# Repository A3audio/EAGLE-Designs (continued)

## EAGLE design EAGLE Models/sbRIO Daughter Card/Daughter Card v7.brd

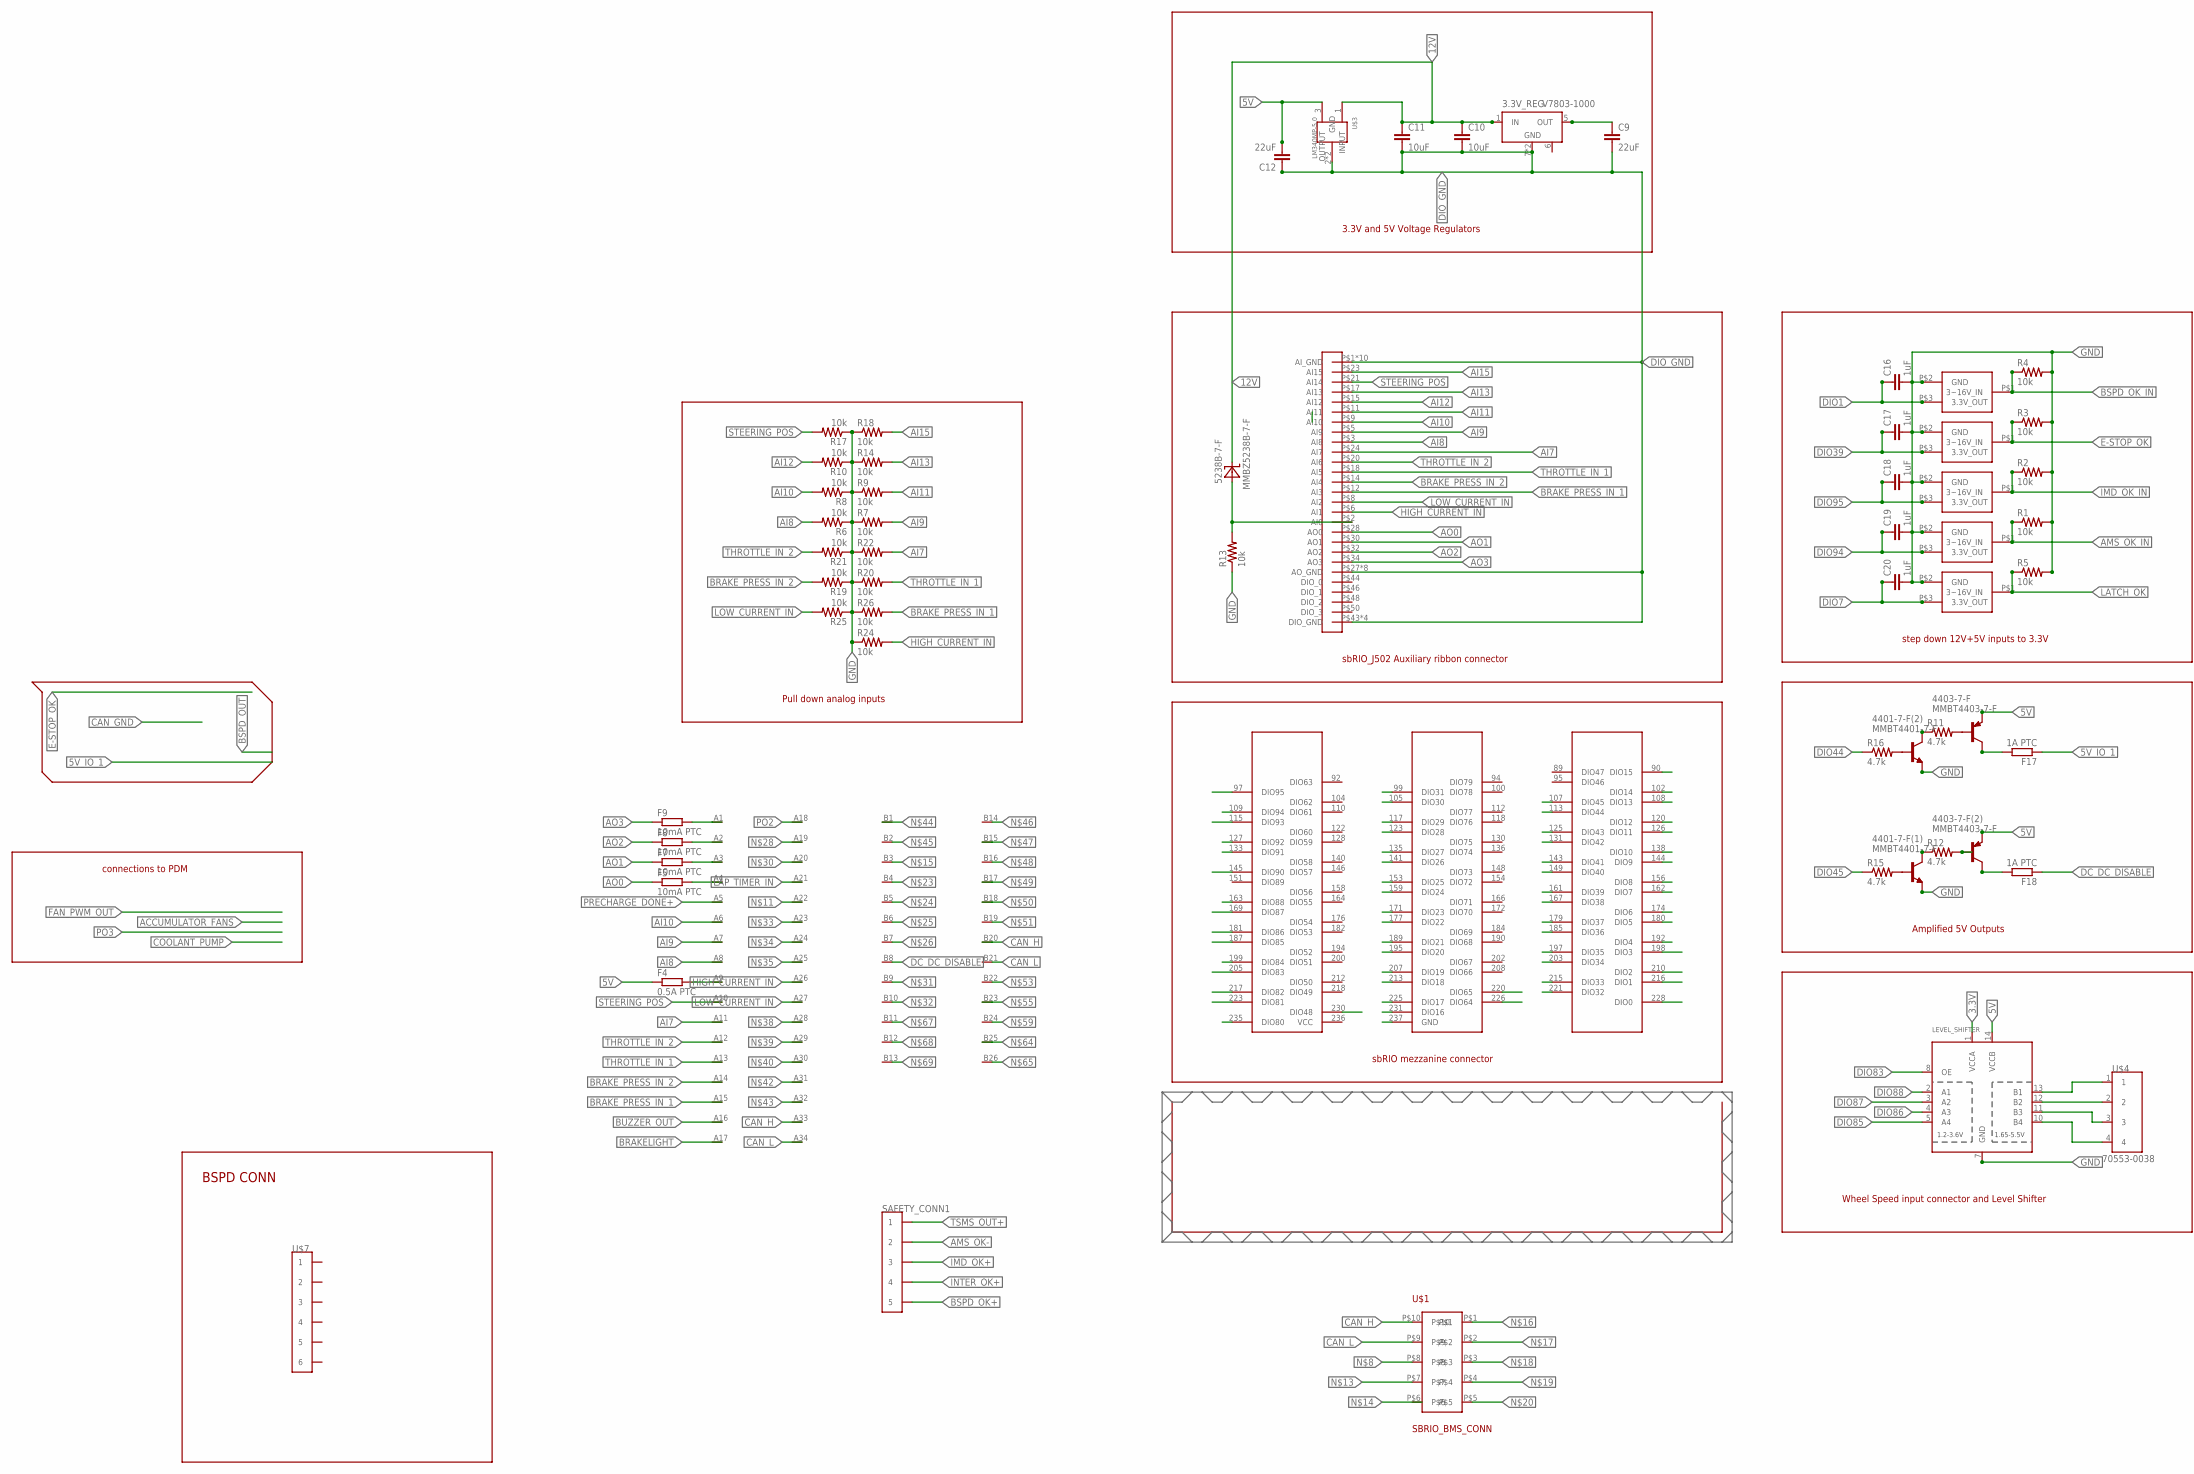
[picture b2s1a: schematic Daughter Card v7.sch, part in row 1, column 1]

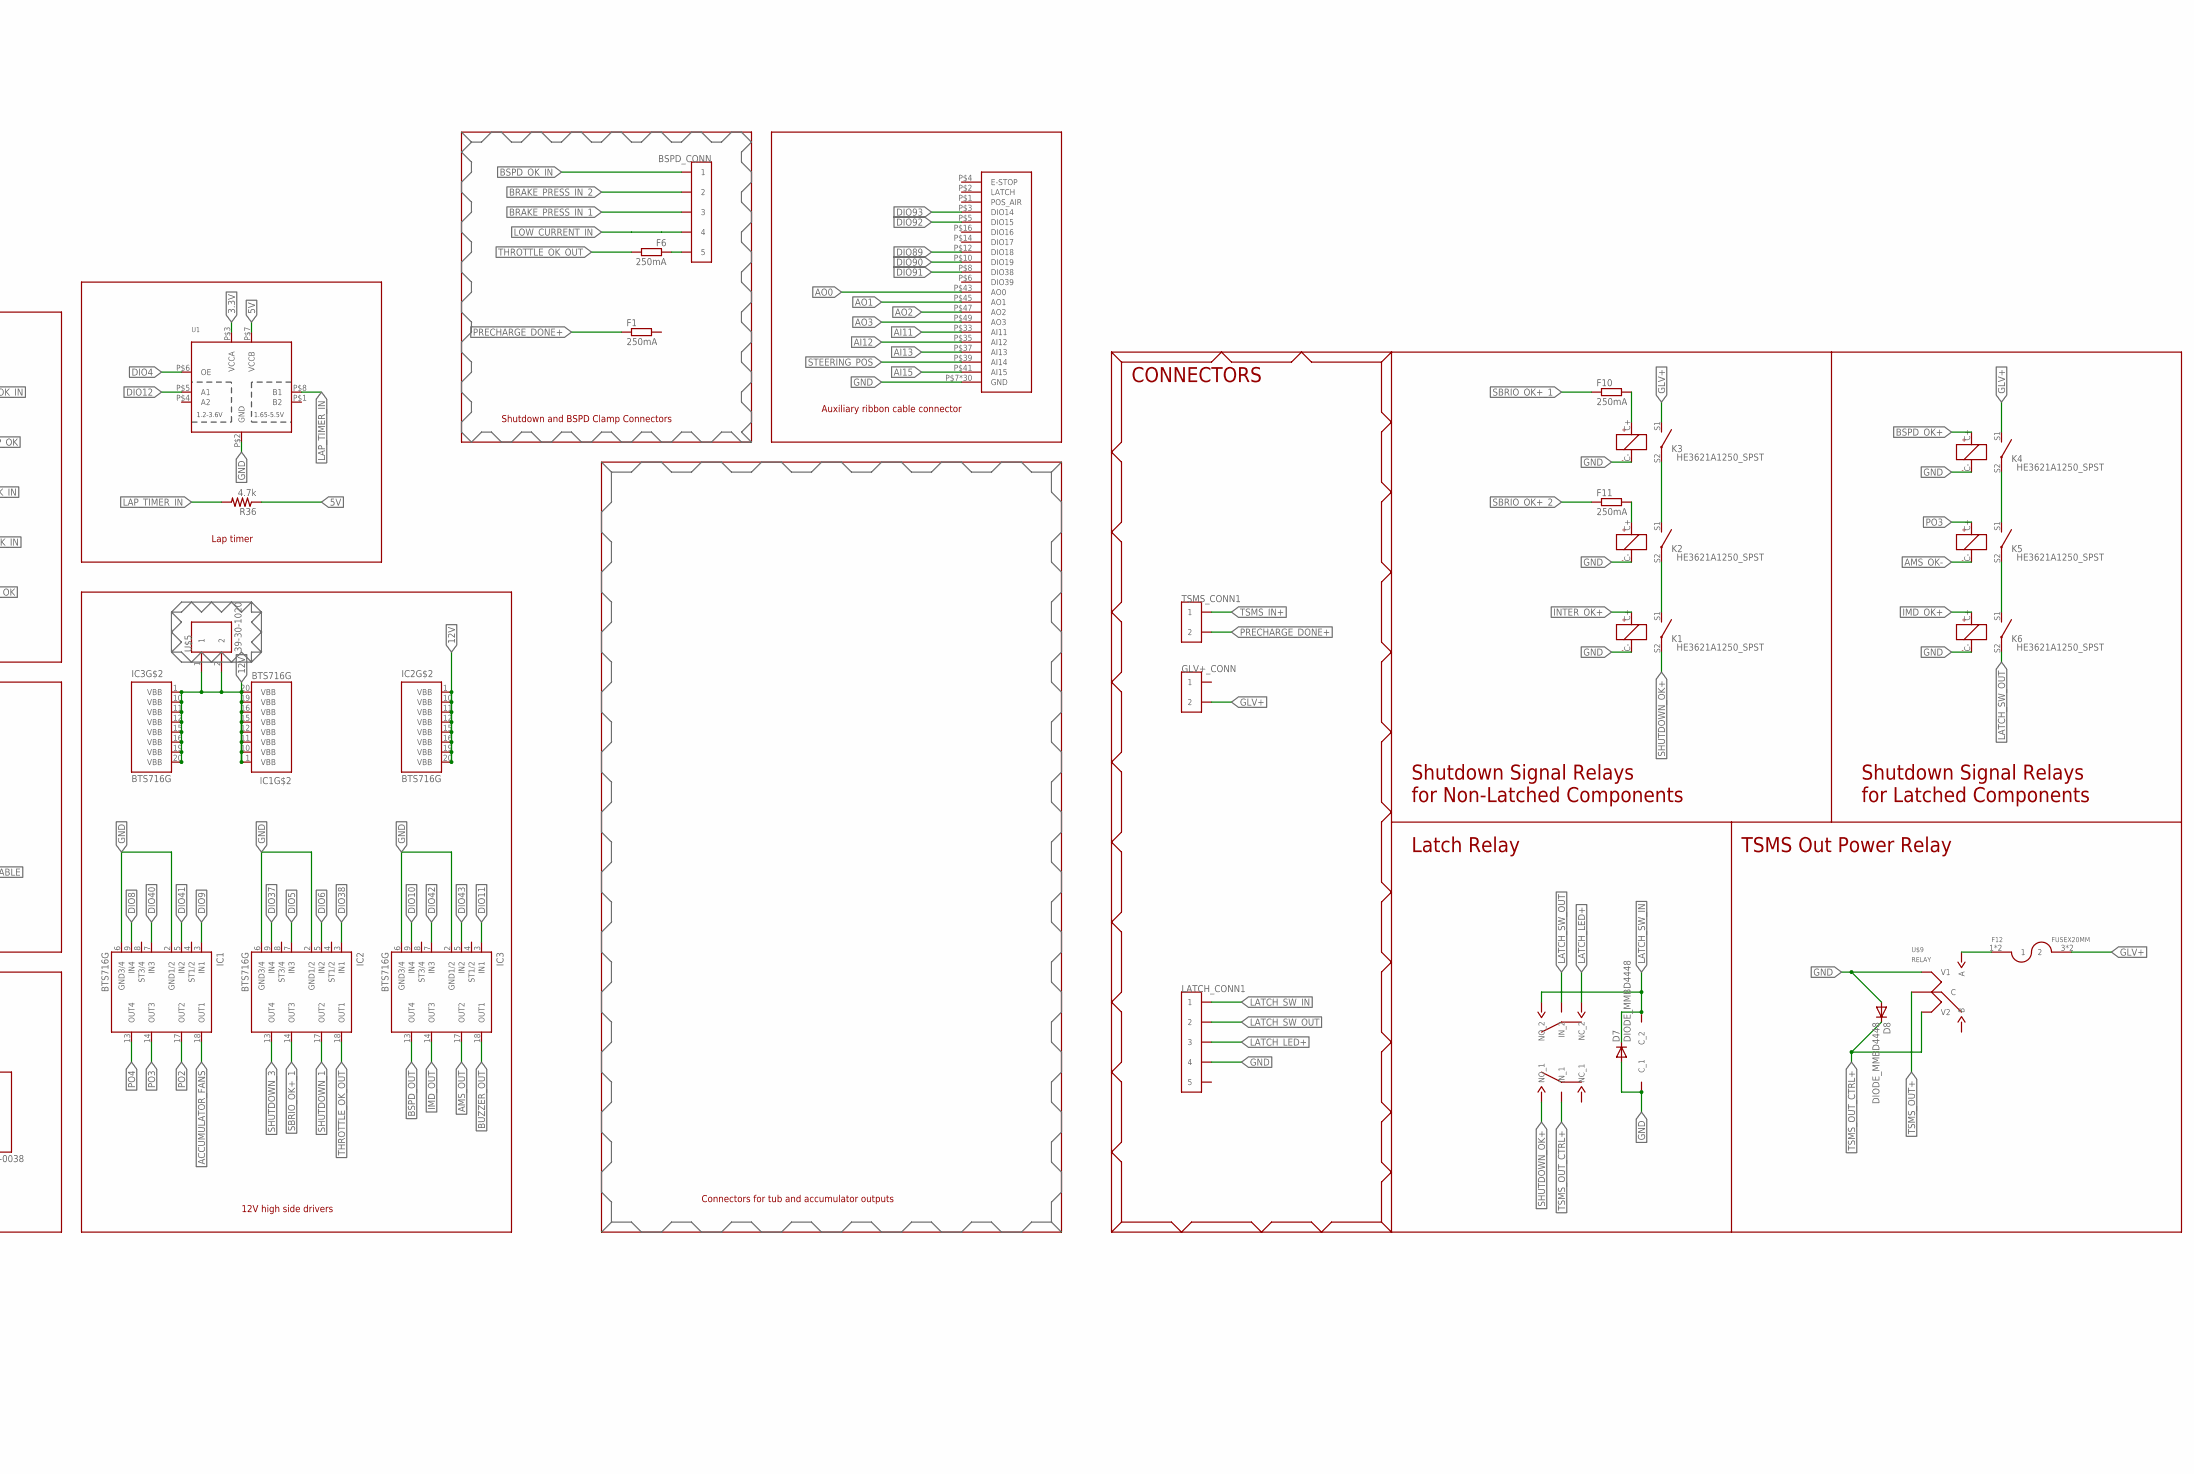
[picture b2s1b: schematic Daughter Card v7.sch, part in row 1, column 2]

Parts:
3.3V_REG: V7803-1000; V78XX-1000
4401-7-F(1), 4401-7-F(2): MMBT4401-7-F; SOT-23-3@1
4403-7-F, 4403-7-F(2): MMBT4403-7-F; SOT-23-3@1
5225-3.3M5-TR(5), 5525-3.3YM5-TR(1), 5525-3.3YM5-TR(2), 5525-3.3YM5-TR(3), 5525-3.3YM5-TR(4): MIC5225-3.3YM5-TR; SOT-23-3@1
5238B-7-F: MMBZ5238B-7-F; SOT-23-3@1
BSPD_CONN: CONN_5; CONNECTOR_5
C9, C12: 22uF; 0603-CAP
C10, C11: 10uF; 0603-CAP
C16, C17, C18, C19, C20: 1uF; 0603-CAP
D7, D8: DIODE_MMBD4448; SOT-23-3
F1, F6, F10, F11: 250mA; R0603
F4: 0.5A PTC; R0603
F5, F7, F8, F9: 10mA PTC; R0402
F12: FUSEX20MM; FUSE_5MM
F17, F18: 1A PTC; R0603
GLV+_CONN: CONN_2; CONNECTOR_2
IC1, IC2, IC3: BTS716G; PG-DSO-20
K1, K2, K3, K4, K5, K6: HE3621A1250_SPST
LATCH_CONN1: CONN_5; CONNECTOR_5
LATCH_U1: JW2SN-DC12V; DPDT_JW2_FORM_C
LEVEL_SHIFTER: TXB0104PWR; TSSOP14
R1, R2, R3, R4, R5, R6, R7, R8, R9, R10, R13, R14, R17, R18, R19, R20, R21, R22, R24, R25, R26: 10k; R0402
R11, R12, R15, R16, R36: 4.7k; R0402
SAFETY_CONN1: CONN_5; CONNECTOR_5
SBRIO_ANALOG: SBRIO_MIO; SBRIO_J502_J503
SBRIO_AUX: SBRIO_AUX; SBRIO_J502_J503
SBRIO_MEZZANINE: SBRIO_RMC; SEAM-40-XX.X-XX-06-X-A
TSMS_CONN1: CONN_2; CONNECTOR_2
U1: TXS0102; VFSOP-8
U$1: SBRIO_BMS_CONN; SBRIO_W
U$3: LM340MP-5.0; SOT223-4
U$4: 70553-0038; MOLEX_70553-0038
U$5: 39-30-1020; MOLEX_39-30-1020
U$6: SUPERSEAL1.0_60POS
U$7: SULLINS_1MM_6P_HEADER; SULLINS_1MM_HEADER
U$9: RELAY

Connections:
3.3V: LEVEL_SHIFTER.1 (VCCA), U1.P$3 (VCCA)
5V: 4403-7-F.P$3 (E), 4403-7-F(2).P$3 (E), C12.2, F4.1, LEVEL_SHIFTER.14 (VCCB), R36.1, U1.P$7 (VCCB), U$3.3 (OUTPUT)
5V_IO_1: F17.1
12V: 3.3V_REG.1 (IN), 5238B-7-F.P$1 (C), C10.1, C11.1, IC1.1 (VBB), IC1.10 (VBB), IC1.11 (VBB), IC1.12 (VBB), IC1.15 (VBB), IC1.16 (VBB), IC1.19 (VBB), IC1.20 (VBB), IC2.1 (VBB), IC2.10 (VBB), IC2.11 (VBB), IC2.12 (VBB), IC2.15 (VBB), IC2.16 (VBB), IC2.19 (VBB), IC2.20 (VBB), IC3.1 (VBB), IC3.10 (VBB), IC3.11 (VBB), IC3.12 (VBB), IC3.15 (VBB), IC3.16 (VBB), IC3.19 (VBB), IC3.20 (VBB), U$3.1 (INPUT), U$5.1, U$5.2
ACCUMULATOR_FANS: IC1.18 (OUT1)
AI7: R22.2, SBRIO_ANALOG.P$24 (AI7), U$6.A11
AI8: R6.2, SBRIO_ANALOG.P$3 (AI8), U$6.A8
AI9: R7.2, SBRIO_ANALOG.P$5 (AI9), U$6.A7
AI10: R8.2, SBRIO_ANALOG.P$9 (AI10), U$6.A6
AI11: R9.2, SBRIO_ANALOG.P$11 (AI11), SBRIO_AUX.P$33 (AI11)
AI12: R10.2, SBRIO_ANALOG.P$15 (AI12), SBRIO_AUX.P$35 (AI12)
AI13: R14.2, SBRIO_ANALOG.P$17 (AI13), SBRIO_AUX.P$37 (AI13)
AI15: R18.2, SBRIO_ANALOG.P$23 (AI15), SBRIO_AUX.P$41 (AI15)
AMS_OK-: K5.C-, SAFETY_CONN1.3 (2), SAFETY_CONN1.4 (2)
AMS_OK_IN: 5525-3.3YM5-TR(1).P$1 (3~16V_IN), R1.1
AMS_OUT: IC3.17 (OUT2)
AO0: F5.1, SBRIO_ANALOG.P$28 (AO0), SBRIO_AUX.P$43 (AO0)
AO1: F7.1, SBRIO_ANALOG.P$30 (AO1), SBRIO_AUX.P$45 (AO1)
AO2: F8.1, SBRIO_ANALOG.P$32 (AO2), SBRIO_AUX.P$47 (AO2)
AO3: F9.1, SBRIO_ANALOG.P$34 (AO3), SBRIO_AUX.P$49 (AO3)
BRAKELIGHT: U$6.A17
BRAKE_PRESS_IN_1: BSPD_CONN.5 (3), BSPD_CONN.6 (3), R26.2, SBRIO_ANALOG.P$12 (AI3), U$6.A15
BRAKE_PRESS_IN_2: BSPD_CONN.3 (2), BSPD_CONN.4 (2), R19.2, SBRIO_ANALOG.P$14 (AI4), U$6.A14
BSPD_OK+: K4.C+, SAFETY_CONN1.9 (5), SAFETY_CONN1.10 (5)
BSPD_OK_IN: 5525-3.3YM5-TR(3).P$1 (3~16V_IN), BSPD_CONN.1, BSPD_CONN.2 (1), R4.1
BSPD_OUT: IC3.13 (OUT4)
BUZZER_OUT: IC3.18 (OUT1), U$6.A16
CAN_H: U$1.P$10, U$6.A33, U$6.B20
CAN_L: U$1.P$9, U$6.A34, U$6.B21
DC_DC_DISABLE: F18.1, U$6.B8
DIO0: SBRIO_MEZZANINE.228 (DIO0)
DIO1: 5525-3.3YM5-TR(3).P$3 (3.3V_OUT), C16.1, SBRIO_MEZZANINE.216 (DIO1)
DIO2: SBRIO_MEZZANINE.210 (DIO2)
DIO3: SBRIO_MEZZANINE.198 (DIO3)
DIO4: SBRIO_MEZZANINE.192 (DIO4), U1.P$6 (OE)
DIO5: IC2.7 (IN3), SBRIO_MEZZANINE.180 (DIO5)
DIO6: IC2.5 (IN2), SBRIO_MEZZANINE.174 (DIO6)
DIO7: 5525-3.3YM5-TR(2).P$3 (3.3V_OUT), C20.1, SBRIO_MEZZANINE.162 (DIO7)
DIO8: IC1.9 (IN4), SBRIO_MEZZANINE.156 (DIO8)
DIO9: IC1.3 (IN1), SBRIO_MEZZANINE.144 (DIO9)
DIO10: IC3.9 (IN4), SBRIO_MEZZANINE.138 (DIO10)
DIO11: IC3.3 (IN1), SBRIO_MEZZANINE.126 (DIO11)
DIO12: SBRIO_MEZZANINE.120 (DIO12), U1.P$5 (A1)
DIO13: SBRIO_MEZZANINE.108 (DIO13)
DIO14: SBRIO_MEZZANINE.102 (DIO14)
DIO15: SBRIO_MEZZANINE.90 (DIO15)
DIO16: SBRIO_MEZZANINE.231 (DIO16)
DIO17: SBRIO_MEZZANINE.225 (DIO17)
DIO18: SBRIO_MEZZANINE.213 (DIO18)
DIO19: SBRIO_MEZZANINE.207 (DIO19)
DIO20: SBRIO_MEZZANINE.195 (DIO20)
DIO21: SBRIO_MEZZANINE.189 (DIO21)
DIO22: SBRIO_MEZZANINE.177 (DIO22)
DIO23: SBRIO_MEZZANINE.171 (DIO23)
DIO24: SBRIO_MEZZANINE.159 (DIO24)
DIO25: SBRIO_MEZZANINE.153 (DIO25)
DIO26: SBRIO_MEZZANINE.141 (DIO26)
DIO27: SBRIO_MEZZANINE.135 (DIO27)
DIO28: SBRIO_MEZZANINE.123 (DIO28)
DIO29: SBRIO_MEZZANINE.117 (DIO29)
DIO30: SBRIO_MEZZANINE.105 (DIO30)
DIO31: SBRIO_MEZZANINE.99 (DIO31)
DIO32: SBRIO_MEZZANINE.221 (DIO32)
DIO33: SBRIO_MEZZANINE.215 (DIO33)
DIO34: SBRIO_MEZZANINE.203 (DIO34)
DIO35: SBRIO_MEZZANINE.197 (DIO35)
DIO36: SBRIO_MEZZANINE.185 (DIO36)
DIO37: IC2.9 (IN4), SBRIO_MEZZANINE.179 (DIO37)
DIO38: IC2.3 (IN1), SBRIO_MEZZANINE.167 (DIO38)
DIO39: 5525-3.3YM5-TR(4).P$3 (3.3V_OUT), C17.1, SBRIO_MEZZANINE.161 (DIO39)
DIO40: IC1.7 (IN3), SBRIO_MEZZANINE.149 (DIO40)
DIO41: IC1.5 (IN2), SBRIO_MEZZANINE.143 (DIO41)
DIO42: IC3.7 (IN3), SBRIO_MEZZANINE.131 (DIO42)
DIO43: IC3.5 (IN2), SBRIO_MEZZANINE.125 (DIO43)
DIO44: R16.1, SBRIO_MEZZANINE.113 (DIO44)
DIO45: R15.1, SBRIO_MEZZANINE.107 (DIO45)
DIO48: SBRIO_MEZZANINE.230 (DIO48)
DIO64: SBRIO_MEZZANINE.226 (DIO64)
DIO65: SBRIO_MEZZANINE.220 (DIO65)
DIO80: SBRIO_MEZZANINE.235 (DIO80)
DIO81: SBRIO_MEZZANINE.223 (DIO81)
DIO82: SBRIO_MEZZANINE.217 (DIO82)
DIO83: LEVEL_SHIFTER.8 (OE), SBRIO_MEZZANINE.205 (DIO83)
DIO84: SBRIO_MEZZANINE.199 (DIO84)
DIO85: LEVEL_SHIFTER.5 (A4), SBRIO_MEZZANINE.187 (DIO85)
DIO86: LEVEL_SHIFTER.4 (A3), SBRIO_MEZZANINE.181 (DIO86)
DIO87: LEVEL_SHIFTER.3 (A2), SBRIO_MEZZANINE.169 (DIO87)
DIO88: LEVEL_SHIFTER.2 (A1), SBRIO_MEZZANINE.163 (DIO88)
DIO89: SBRIO_AUX.P$12 (DIO18)
DIO90: SBRIO_AUX.P$10 (DIO19), SBRIO_MEZZANINE.145 (DIO90)
DIO91: SBRIO_AUX.P$8 (DIO38), SBRIO_MEZZANINE.133 (DIO91)
DIO92: SBRIO_AUX.P$5 (DIO15), SBRIO_MEZZANINE.127 (DIO92)
DIO93: SBRIO_AUX.P$3 (DIO14), SBRIO_MEZZANINE.115 (DIO93)
DIO94: 5525-3.3YM5-TR(1).P$3 (3.3V_OUT), C19.1, SBRIO_MEZZANINE.109 (DIO94)
DIO95: 5225-3.3M5-TR(5).P$3 (3.3V_OUT), C18.1, SBRIO_MEZZANINE.97 (DIO95)
DIO_GND: 3.3V_REG.7 (GND), 3.3V_REG.9 (GND), C9.2, C10.2, C11.2, C12.1, SBRIO_ANALOG.P$1 (AI_GND), SBRIO_ANALOG.P$4 (AI_GND), SBRIO_ANALOG.P$7 (AI_GND), SBRIO_ANALOG.P$10 (AI_GND), SBRIO_ANALOG.P$13 (AI_GND), SBRIO_ANALOG.P$16 (AI_GND), SBRIO_ANALOG.P$19 (AI_GND), SBRIO_ANALOG.P$22 (AI_GND), SBRIO_ANALOG.P$25 (AI_GND), SBRIO_ANALOG.P$26 (AI_GND), SBRIO_ANALOG.P$27 (AO_GND), SBRIO_ANALOG.P$29 (AO_GND), SBRIO_ANALOG.P$31 (AO_GND), SBRIO_ANALOG.P$33 (AO_GND), SBRIO_ANALOG.P$35 (AO_GND), SBRIO_ANALOG.P$37 (AO_GND), SBRIO_ANALOG.P$39 (AO_GND), SBRIO_ANALOG.P$41 (AO_GND), SBRIO_ANALOG.P$43 (DIO_GND), SBRIO_ANALOG.P$45 (DIO_GND), SBRIO_ANALOG.P$47 (DIO_GND), SBRIO_ANALOG.P$49 (DIO_GND), U$3.2 (GND), U$3.4 (GND)
E-STOP_OK: 5525-3.3YM5-TR(4).P$1 (3~16V_IN), R3.1
GLV+: F12.3 (2), F12.4 (2), GLV+_CONN.3 (2), GLV+_CONN.4 (2), K3.S1 (SW_1), K4.S1 (SW_1)
GND: 4401-7-F(1).P$3 (E), 4401-7-F(2).P$3 (E), 5225-3.3M5-TR(5).P$2 (GND), 5525-3.3YM5-TR(1).P$2 (GND), 5525-3.3YM5-TR(2).P$2 (GND), 5525-3.3YM5-TR(3).P$2 (GND), 5525-3.3YM5-TR(4).P$2 (GND), C16.2, C17.2, C18.2, C19.2, C20.2, D7.P$2 (A), D8.P$2 (A), IC1.2 (GND1/2), IC1.6 (GND3/4), IC2.2 (GND1/2), IC2.6 (GND3/4), IC3.2 (GND1/2), IC3.6 (GND3/4), K1.C-, K2.C-, K3.C-, K4.C-, K6.C-, LATCH_CONN1.7 (4), LATCH_CONN1.8 (4), LATCH_U1.COIL_1 (C_1), LEVEL_SHIFTER.7 (GND), R1.2, R2.2, R3.2, R4.2, R5.2, R6.1, R7.1, R8.1, R9.1, R10.1, R13.1, R14.1, R17.1, R18.1, R19.1, R20.1, R21.1, R22.1, R24.1, R25.1, R26.1, SBRIO_AUX.P$7 (GND), SBRIO_AUX.P$9 (GND), SBRIO_AUX.P$11 (GND), SBRIO_AUX.P$13 (GND), SBRIO_AUX.P$15 (GND), SBRIO_AUX.P$17 (GND), SBRIO_AUX.P$18 (GND), SBRIO_AUX.P$19 (GND), SBRIO_AUX.P$20 (GND), SBRIO_AUX.P$21 (GND), SBRIO_AUX.P$22 (GND), SBRIO_AUX.P$23 (GND), SBRIO_AUX.P$24 (GND), SBRIO_AUX.P$25 (GND), SBRIO_AUX.P$26 (GND), SBRIO_AUX.P$27 (GND), SBRIO_AUX.P$28 (GND), SBRIO_AUX.P$29 (GND), SBRIO_AUX.P$30 (GND), SBRIO_AUX.P$31 (GND), SBRIO_AUX.P$32 (GND), SBRIO_AUX.P$34 (GND), SBRIO_AUX.P$36 (GND), SBRIO_AUX.P$38 (GND), SBRIO_AUX.P$40 (GND), SBRIO_AUX.P$42 (GND), SBRIO_AUX.P$44 (GND), SBRIO_AUX.P$46 (GND), SBRIO_AUX.P$48 (GND), SBRIO_AUX.P$50 (GND), SBRIO_MEZZANINE.237 (GND), U1.P$2 (GND), U$9.V1
HIGH_CURRENT_IN: R24.2, SBRIO_ANALOG.P$6 (AI1), U$6.A26
IMD_OK+: K6.C+, SAFETY_CONN1.5 (3), SAFETY_CONN1.6 (3)
IMD_OK_IN: 5225-3.3M5-TR(5).P$1 (3~16V_IN), R2.1
IMD_OUT: IC3.14 (OUT3)
INTER_OK+: K1.C+, SAFETY_CONN1.7 (4), SAFETY_CONN1.8 (4)
K4: K4.S2 (SW_2), K5.S1 (SW_1)
LAP_TIMER_IN: R36.2, U1.P$8 (B1), U$6.A21
LATCH_LED+: LATCH_CONN1.5 (3), LATCH_CONN1.6 (3), LATCH_U1.NC_2
LATCH_OK: 5525-3.3YM5-TR(2).P$1 (3~16V_IN), R5.1
LATCH_SW_IN: D7.P$1 (C), LATCH_CONN1.1, LATCH_CONN1.2 (1), LATCH_U1.COIL_2 (C_2), LATCH_U1.NO_2
LATCH_SW_OUT: K6.S2 (SW_2), LATCH_CONN1.3 (2), LATCH_CONN1.4 (2), LATCH_U1.CENTER_2 (IN_2)
LOW_CURRENT_IN: BSPD_CONN.7 (4), BSPD_CONN.8 (4), R25.2, SBRIO_ANALOG.P$8 (AI2), U$6.A27
unnamed: K2.S1 (SW_1), K3.S2 (SW_2)
unnamed: 5238B-7-F.P$2 (A), R13.2, SBRIO_ANALOG.P$2 (AI0)
unnamed: 3.3V_REG.5 (OUT), C9.1
unnamed: K1.S1 (SW_1), K2.S2 (SW_2)
unnamed: K5.S2 (SW_2), K6.S1 (SW_1)
unnamed: F12.1, F12.2 (1), U$9.A
unnamed: F4.2, U$6.A9
unnamed: BSPD_CONN.9 (5), BSPD_CONN.10 (5), F6.1
unnamed: 4403-7-F.P$2 (B), R11.2
unnamed: 4403-7-F.P$1 (C), F17.2
unnamed: 4403-7-F(2).P$1 (C), F18.2
unnamed: 4403-7-F(2).P$2 (B), R12.2
unnamed: 4401-7-F(1).P$2 (B), R15.2
unnamed: 4401-7-F(1).P$1 (C), R12.1
unnamed: 4401-7-F(2).P$2 (B), R16.2
unnamed: 4401-7-F(2).P$1 (C), R11.1
unnamed: F5.2, U$6.A4
unnamed: F7.2, U$6.A3
unnamed: F8.2, U$6.A2
unnamed: F9.2, U$6.A1
PO2: IC1.17 (OUT2), U$6.A18
PO3: IC1.14 (OUT3), K5.C+
PO4: IC1.13 (OUT4)
PRECHARGE_DONE+: F1.1, TSMS_CONN1.3 (2), TSMS_CONN1.4 (2), U$6.A5
SBRIO_OK+_1: F10.1, IC2.14 (OUT3)
SBRIO_OK+_1_RELAY_IN1: F10.2, K3.C+
SBRIO_OK+_2: F11.1
SBRIO_OK_2_RELAY1: F11.2, K2.C+
SHUTDOWN_1: IC2.17 (OUT2)
SHUTDOWN_3: IC2.13 (OUT4)
SHUTDOWN_OK+: K1.S2 (SW_2), LATCH_U1.NO_1
STEERING_POS: R17.2, SBRIO_ANALOG.P$21 (AI14), SBRIO_AUX.P$39 (AI14), U$6.A10
THROTTLE_IN_1: R20.2, SBRIO_ANALOG.P$18 (AI5), U$6.A13
THROTTLE_IN_2: R21.2, SBRIO_ANALOG.P$20 (AI6), U$6.A12
THROTTLE_OK_OUT: F6.2, IC2.18 (OUT1)
TSMS_IN+: TSMS_CONN1.1, TSMS_CONN1.2 (1)
TSMS_OUT+: SAFETY_CONN1.1, SAFETY_CONN1.2 (1), U$9.CENTER (C)
TSMS_OUT_CTRL+: D8.P$1 (C), LATCH_U1.CENTER_1 (IN_1), U$9.V2
VCC: SBRIO_MEZZANINE.236 (VCC)
WS1: LEVEL_SHIFTER.13 (B1), U$4.1
WS2: LEVEL_SHIFTER.12 (B2), U$4.2
WS3: LEVEL_SHIFTER.11 (B3), U$4.3
WS4: LEVEL_SHIFTER.10 (B4), U$4.4

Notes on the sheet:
step down 12V+5V inputs to 3.3V
Auxiliary ribbon cable connector
Amplified 5V Outputs
sbRIO mezzanine connector
sbRIO_J502 Auxiliary ribbon connector
3.3V and 5V Voltage Regulators
Wheel Speed input connector and Level Shifter
Shutdown and BSPD Clamp Connectors
12V high side drivers
Lap timer
Connectors for tub and accumulator outputs
Pull down analog inputs
connections to PDM
CONNECTORS
Shutdown Signal Relays for Non-Latched Components
Shutdown Signal Relays for Latched Components
Latch Relay
TSMS Out Power Relay
BSPD CONN

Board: 2 copper layers, 87 parts (0 on the bottom side), 108 nets, no tracks yet.

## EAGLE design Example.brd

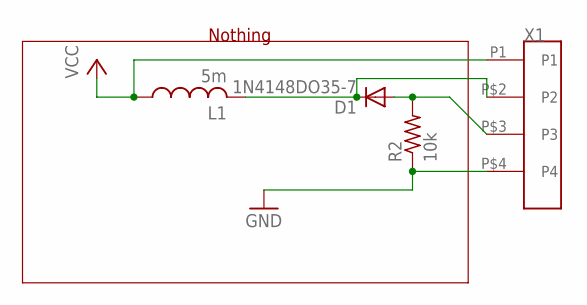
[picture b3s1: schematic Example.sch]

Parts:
D1: 1N4148DO35-7; DO35-7
L1: 5m; L3225P
R2: 10k; M0805
X1: TE-952

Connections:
GND: R2.1, X1.P$4 (P4)
unnamed: D1.C, L1.2, X1.P$2 (P2)
unnamed: D1.A, R2.2, X1.P$3 (P3)
VCC: L1.1, X1.P1

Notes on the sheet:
Nothing

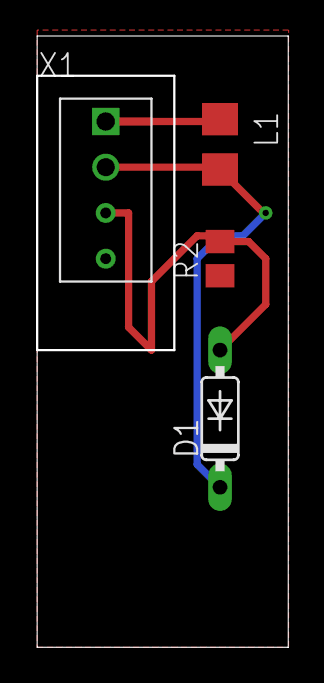
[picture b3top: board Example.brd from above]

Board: 2 copper layers, 13.9 x 34.0 mm, 4 parts (0 on the bottom side), 4 nets.
